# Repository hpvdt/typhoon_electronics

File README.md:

# Typhoon Electronics

The electronics system for Typhoon Streamliner

## Organization

There is a folder for each subsystem. Within each subsystem folder are `hardware` and `firmware` folders. Put hardware related files into the `hardware` folder, firmware in the `firmware` folder. Other folders can be added as needed: for example a `media` folder is handy for storing pictures related to a project which can be used in documentation.

## Conventions

Partly for consistency, partly for functionality; please follow the following conventions:

- Try to keep folder names to single words and all lowercase
- Use underscores to separate words in names (e.g. `board_rev1`). **DO NOT USE SPACES! ESPECIALLY FOR FOLDERS CONTAINING CODE!** Spaces in file paths may cause issues in compilers and such so best to avoid them entirely.

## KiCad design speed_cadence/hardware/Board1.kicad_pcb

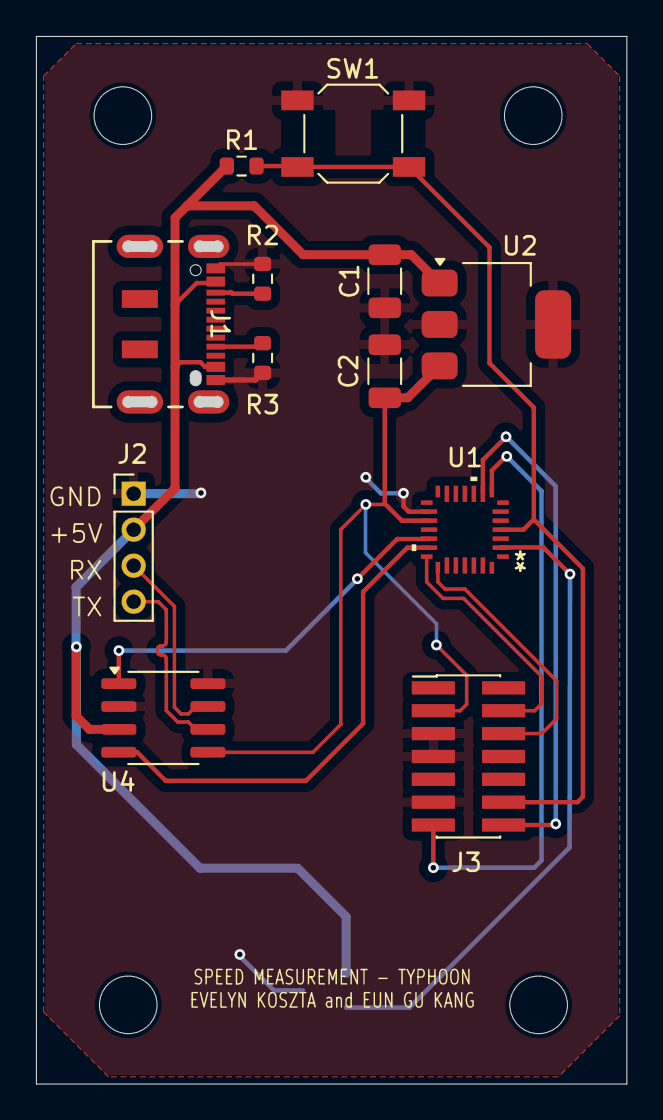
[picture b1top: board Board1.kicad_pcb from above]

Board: 2 copper layers, 32.8 x 58.2 mm, 17 parts (1 on the bottom side), 15 nets.

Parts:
C1: 0.47u; C_1206_3216Metric
C2: 22u; C_1206_3216Metric
H1, H2, H3, H4: MountingHole; MountingHole_3.2mm_M3_ISO14580
IC1: AH1912-W-7; SC-59
J1: DX07S016JA3R1500; CONN12_DX07S_JAE
J2: Conn_01x04_Pin; PinHeader_1x04_P2.00mm_Vertical
J3: Conn_ST_STDC14; PinHeader_2x07_P1.27mm_Vertical_SMD
R1: 10K; R_0603_1608Metric
R2, R3: 5.1k; R_0603_1608Metric
SW1: SW_Push; SW_SPST_SKQG_WithStem
U1: STM32F042G6U6TR; UFQFPN28-4x4mm-M
U2: TS2940CW33_RPG; SOT-223-3_TabPin2
U4: TJA1051T-3; SOIC-8_3.9x4.9mm_P1.27mm

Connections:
+3V3: C2.1, J3.3 (VCC), U1.17 (VDD), U2.3 (OUTPUT), U4.5 (VIO)
+5V: C1.1, IC1.1 (VDD), J1.2 (VBUS), J1.11 (VBUS), J2.2, R1.1, U2.1 (INPUT), U4.3 (VCC)
CAN+: J2.3, U4.7 (CANH)
CAN-: J2.4, U4.6 (CANL)
CAN_RX: U1.20 (PA10/PA12), U4.4 (RXD)
CAN_TX: U1.19 (PA9/PA11), U4.1 (TXD)
GND: C1.2, C2.2, IC1.3 (GND), J1.1 (GND), J1.12 (GND), J2.1, J3.5 (GND), J3.7 (GND), J3.11 (GNDDetect), R2.2, R3.2, SW1.2, U1.16 (VSS), U2.2 (GROUND_1), U4.2 (GND), U4.8 (S)
unnamed: IC1.2 (OUTPUT), U1.2 (PF0-OSC_IN)
unnamed: J1.3 (CC1), R2.1
unnamed: J1.9 (CC2), R3.1
Prog_RX: J3.13 (VCP_RX), U1.8 (PA2)
Prog_TX: J3.14 (VCP_TX), U1.9 (PA3)
RESET_PROG: J3.12 (~RST), R1.2, SW1.1, U1.4 (NRST)
codeclk: J3.6 (JCLK/SWCLK), U1.22 (PA14)
codeio: J3.4 (JTMS/SWDIO), U1.21 (PA13)

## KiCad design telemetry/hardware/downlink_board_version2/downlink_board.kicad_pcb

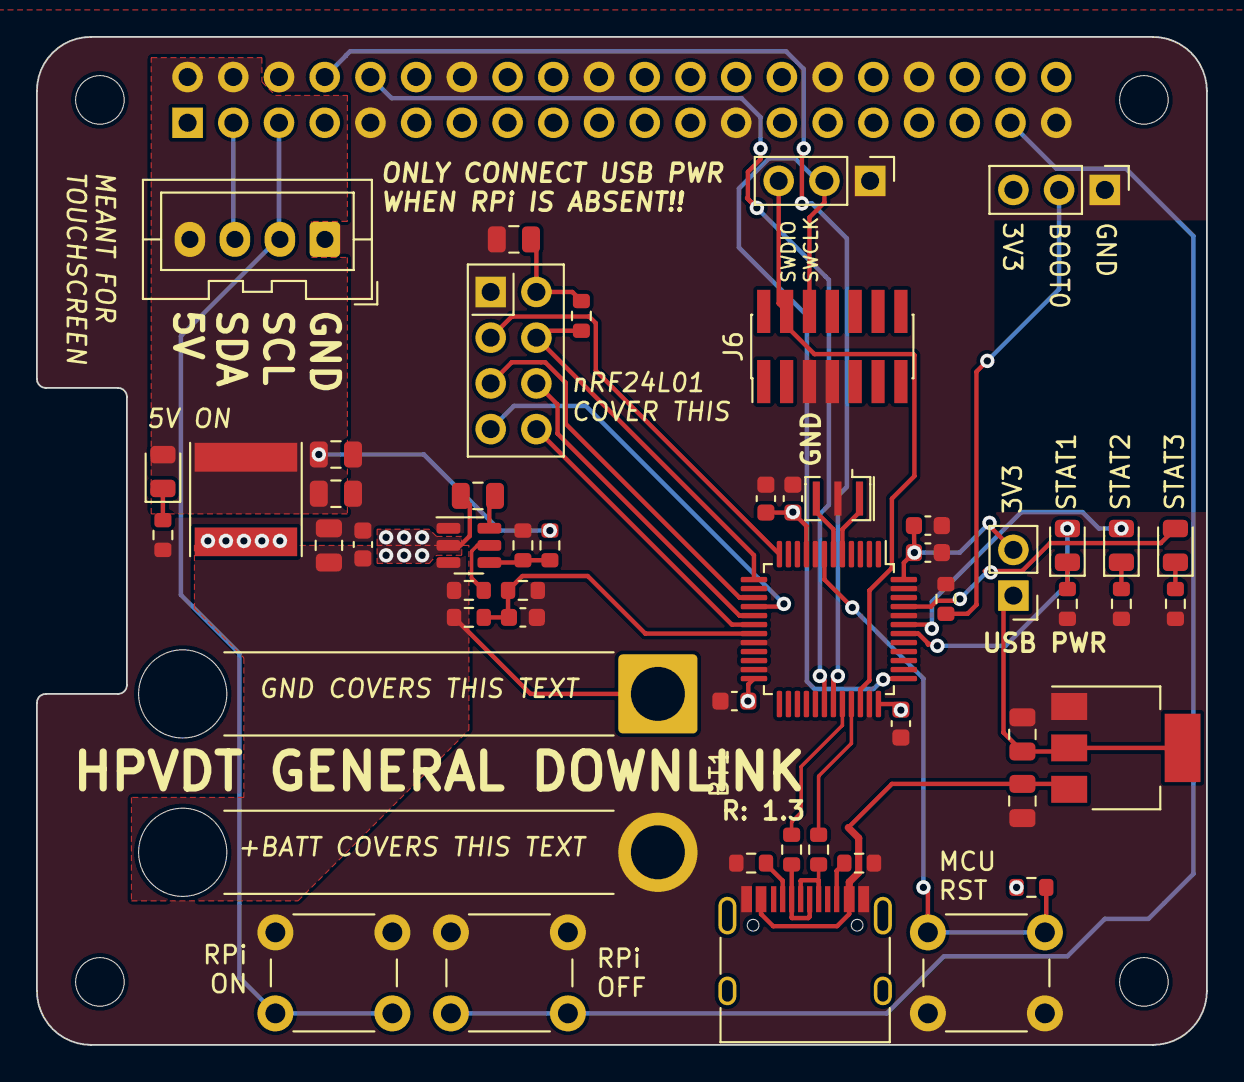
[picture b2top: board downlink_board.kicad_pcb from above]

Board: 2 copper layers, 65.0 x 56.0 mm, 56 parts (1 on the bottom side), 41 nets.

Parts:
BT1: Battery; SolderWire-2.5sqmm_1x02_P8.8mm_D2.4mm_OD4.4mm_Relief
C1, C2, C14: 10u; C_0805_2012Metric
C3, C8, C9, C10, C11, C13: 100n; C_0603_1608Metric
C4, C6, C7: 22u; C_0805_2012Metric
C5: 100n; C_0805_2012Metric
C12: 10n; C_0603_1608Metric
C15: 1u; C_0603_1608Metric
D1, D2, D3, D4: LED; LED_0805_2012Metric
J1: USB_C_Receptacle_USB2.0; USB_C_Receptacle_HRO_TYPE-C-31-M-12
J2: SCREEN; JST_XA_B04B-XASK-1_1x04_P2.50mm_Vertical
J3: GPIO; PinSocket_2x20_P2.54mm_Vertical
J4: PROGRAM; PinHeader_1x03_P2.54mm_Vertical
J6: Conn_ST_STDC14; PinHeader_2x07_P1.27mm_Vertical_SMD
JP1: USB_PWR; PinHeader_1x02_P2.54mm_Vertical
JP2: BOOT0; PinHeader_1x03_P2.54mm_Vertical
L1: 3u3; L_Taiyo-Yuden_NR-60xx
MH1, MH2, MH3, MH4: MountingHole_2.7mm_M2.5
R1, R2: 5.1k; R_0603_1608Metric
R3, R4: 22; R_0603_1608Metric
R5, R7, R9, R13, R14, R16: 10k; R_0603_1608Metric
R6, R15: 54k9; R_0603_1608Metric
R8, R10, R11, R12: 330; R_0603_1608Metric
SW1: RPi_{ON}; SW_PUSH_6mm_H4.3mm
SW2: RPi_{OFF}; SW_PUSH_6mm_H4.3mm
SW3: MCU_{RST}; SW_PUSH_6mm_H4.3mm
U1: AZ1117-3.3; SOT-223-3_TabPin2
U2: TPS563208DDCR; TSOT-23-6
U3: STM32F103C8Tx; LQFP-48_7x7mm_P0.5mm
U4: nRF24L01; nRF24L01_Breakout
Y1: 8M; Resonator_SMD_Murata_CSTxExxV-3Pin_3.0x1.1mm

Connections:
+3.3V: C8.2, C9.2, C10.2, C11.2, C12.2, C14.2, C15.2, J3.1, J3.17, JP1.2 (B), JP2.3 (B), R13.2, R14.2, U3.9 (VDDA), U3.24 (VDD), U3.36 (VDD), U3.48 (VDD), U4.2 (VCC)
+5V: C6.2, C7.2, D2.2 (A), J2.4, J3.2, J3.4, L1.2, R6.1
+BATT: BT1.1 (+), C1.2, C3.2, R5.1, R15.2, U2.3 (VIN)
/BATT_{DIV}: C13.2, R15.1, R16.2, U3.19 (PB1)
/BOOT0: JP2.2 (C), R9.2
/D+: J1.A6 (D+), J1.B6 (D+), R4.1
/D-: J1.A7 (D-), J1.B7 (D-), R3.1
/FB: R6.2, R7.2, U2.4 (VFB)
/GPIO26: J3.37, SW2.2
/MISO: U3.16 (PA6), U4.7 (MISO)
/MOSI: U3.17 (PA7), U4.6 (MOSI)
/RF_{EN}: U3.12 (PA2), U4.3 (CE)
/RF_{INT}: U3.18 (PB0), U4.8 (IRQ)
/RF_{SEL}: R14.1, U3.13 (PA3), U4.4 (~CSN)
/RPi_{RX}: J3.10, U3.30 (PA9)
/RPi_{TX}: J3.8, U3.31 (PA10)
/RST_{MCU}: R13.1, SW3.2, U3.7 (NRST)
/SCK: U3.15 (PA5), U4.5 (SCK)
/SCL: J2.2, J3.5, SW1.2
/SDA: J2.3, J3.3
/SDWIO: J4.3, J6.4 (JTMS/SWDIO), U3.34 (PA13)
/STATUS_{1}: D1.2 (A), U3.42 (PB6)
/STATUS_{2}: D3.2 (A), U3.43 (PB7)
/STATUS_{3}: D4.2 (A), U3.45 (PB8)
/SWCLK: J4.2, J6.6 (JCLK/SWCLK), U3.37 (PA14)
/USB_D+: R4.2, U3.33 (PA12)
/USB_D-: R3.2, U3.32 (PA11)
GND: BT1.2 (-), C1.1, C2.1, C3.1, C4.1, C6.1, C7.1, C8.1, C9.1, C10.1, C11.1, C12.1, C13.1, C14.1, C15.1, J1.A1 (GND), J1.A12 (GND), J1.B1 (GND), J1.B12 (GND), J2.1, J3.6, J3.9, J3.14, J3.20, J3.25, J3.30, J3.34, J3.39, J4.1, J6.5 (GND), J6.7 (GND), JP2.1 (A), R1.2, R2.2, R7.1, R8.1, R9.1, R10.1, R11.1, R12.1, R16.1, SW1.1, SW2.1, SW3.1, U1.1 (GND), U2.1 (GND), U3.8 (VSSA), U3.20 (PB2), U3.23 (VSS), U3.35 (VSS), U3.44 (BOOT0), U3.47 (VSS), U4.1 (GND), Y1.2
unnamed: D1.1 (K), R8.2
unnamed: D2.1 (K), R10.2
unnamed: D3.1 (K), R11.2
unnamed: D4.1 (K), R12.2
unnamed: J1.A5 (CC1), R1.1
unnamed: J1.B5 (CC2), R2.1
unnamed: C4.2, JP1.1 (A), U1.2 (VO)
unnamed: C2.2, J1.A4 (VBUS), J1.A9 (VBUS), J1.B4 (VBUS), J1.B9 (VBUS), U1.3 (VI)
unnamed: R5.2, U2.5 (EN)
unnamed: C5.2, L1.1, U2.2 (SW)
unnamed: C5.1, U2.6 (VBST)
unnamed: U3.5 (PD0), Y1.1
unnamed: U3.6 (PD1), Y1.3

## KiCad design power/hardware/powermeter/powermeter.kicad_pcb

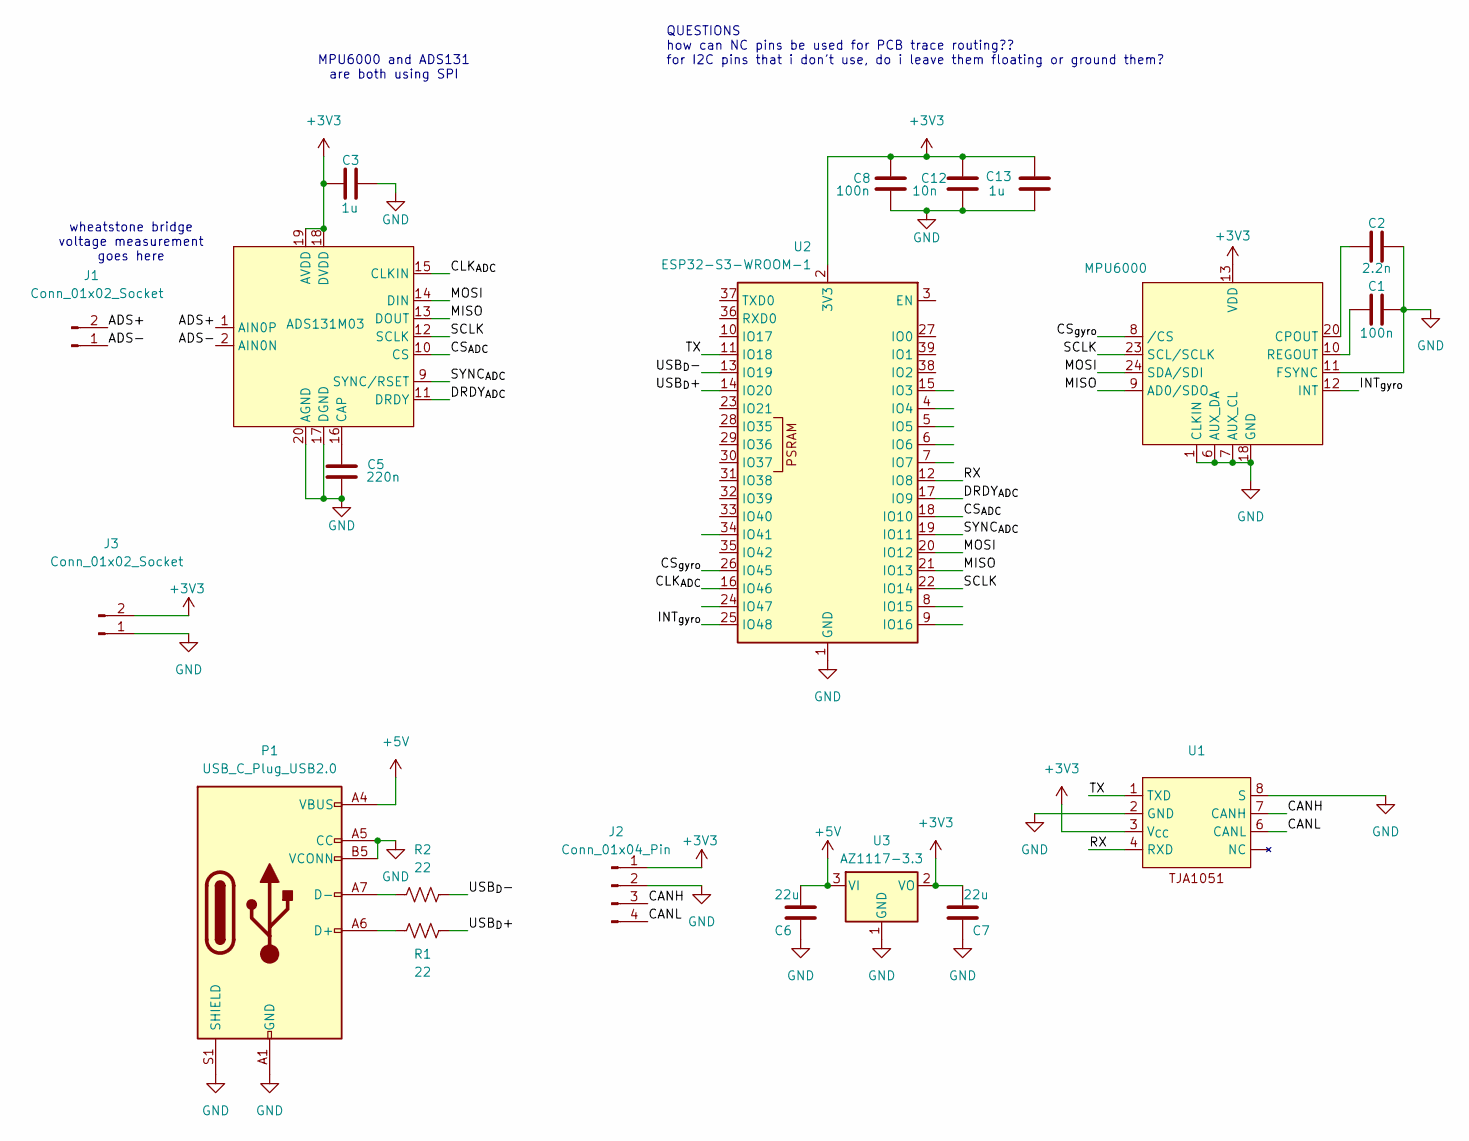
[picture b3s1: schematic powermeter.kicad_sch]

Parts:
ADS131M03: ads
C1, C8: 100n; C_0603_1608Metric
C2: 2.2n; C_0603_1608Metric
C3, C13: 1u; C_0603_1608Metric
C5: 220n; C_0603_1608Metric
C6, C7: 22u; C_0603_1608Metric
C12: 10n; C_0603_1608Metric
J1: Conn_01x02_Socket; PinHeader_1x02_P2.00mm_Vertical
J2: Conn_01x04_Pin; PinHeader_1x04_P2.00mm_Vertical
J3: Conn_01x02_Socket; AMASS_XT30U-M_1x02_P5.0mm_Vertical
MPU6000: QFN24_4X4X0P9_IVS
P1: USB_C_Plug_USB2.0; USB_C_Receptacle_HRO_TYPE-C-31-M-12
R1, R2: 22; R_0603_1608Metric
U1: SO-8_3.9x4.9mm_P1.27mm
U2: ESP32-S3-WROOM-1
U3: AZ1117-3.3; SOT-223-3_TabPin2

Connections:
+3V3: ADS131M03.18 (DVDD), ADS131M03.19 (AVDD), C3.2, C7.2, C8.2, C12.2, C13.2, J2.1, J3.2, MPU6000.13 (VDD), U1.3 (V_{CC}), U2.2 (3V3), U3.2 (VO)
+5V: C6.2, P1.A4 (VBUS), P1.A9 (VBUS), P1.B4 (VBUS), P1.B9 (VBUS), U3.3 (VI)
/ADS+: ADS131M03.1 (AIN0P), J1.2
/ADS-: ADS131M03.2 (AIN0N), J1.1
/CANH: J2.3, U1.7 (CANH)
/CANL: J2.4, U1.6 (CANL)
/CLK_{ADC}: ADS131M03.15 (CLKIN), U2.16 (IO46)
/CS_{ADC}: ADS131M03.10 (CS), U2.18 (IO10)
/CS_{gyro}: MPU6000.8 (/CS), U2.26 (IO45)
/DRDY_{ADC}: ADS131M03.11 (DRDY), U2.17 (IO9)
/INT_{gyro}: MPU6000.12 (INT), U2.25 (IO48)
/MISO: ADS131M03.13 (DOUT), MPU6000.9 (AD0/SDO), U2.21 (IO13)
/MOSI: ADS131M03.14 (DIN), MPU6000.24 (SDA/SDI), U2.20 (IO12)
/RX: U1.4 (RXD), U2.12 (IO8)
/SCLK: ADS131M03.12 (SCLK), MPU6000.23 (SCL/SCLK), U2.22 (IO14)
/SYNC_{ADC}: ADS131M03.9 (SYNC/RSET), U2.19 (IO11)
/TX: U1.1 (TXD), U2.11 (IO18)
/USB_{D}+: R1.2, U2.14 (IO20)
/USB_{D}-: R2.2, U2.13 (IO19)
GND: ADS131M03.17 (DGND), ADS131M03.20 (AGND), C1.1, C2.1, C3.1, C5.1, C6.1, C7.1, C8.1, C12.1, C13.1, J2.2, J3.1, MPU6000.1 (CLKIN), MPU6000.6 (AUX_DA), MPU6000.7 (AUX_CL), MPU6000.11 (FSYNC), MPU6000.18 (GND), P1.A1 (GND), P1.A5 (CC), P1.A12 (GND), P1.B1 (GND), P1.B5 (VCONN), P1.B12 (GND), P1.S1 (SHIELD), U1.2 (GND), U1.8 (S), U2.1 (GND), U2.40 (GND), U2.41 (GND), U3.1 (GND)
unnamed: ADS131M03.16 (CAP), C5.2
unnamed: C2.2, MPU6000.20 (CPOUT)
unnamed: C1.2, MPU6000.10 (REGOUT)
unnamed: P1.A6 (D+), R1.1
unnamed: P1.A7 (D-), R2.1

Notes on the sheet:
wheatstone bridge voltage measurement goes here
MPU6000 and ADS131 are both using SPI
QUESTIONS how can NC pins be used for PCB trace routing?? for I2C pins that i don't use, do i leave them floating or ground them?

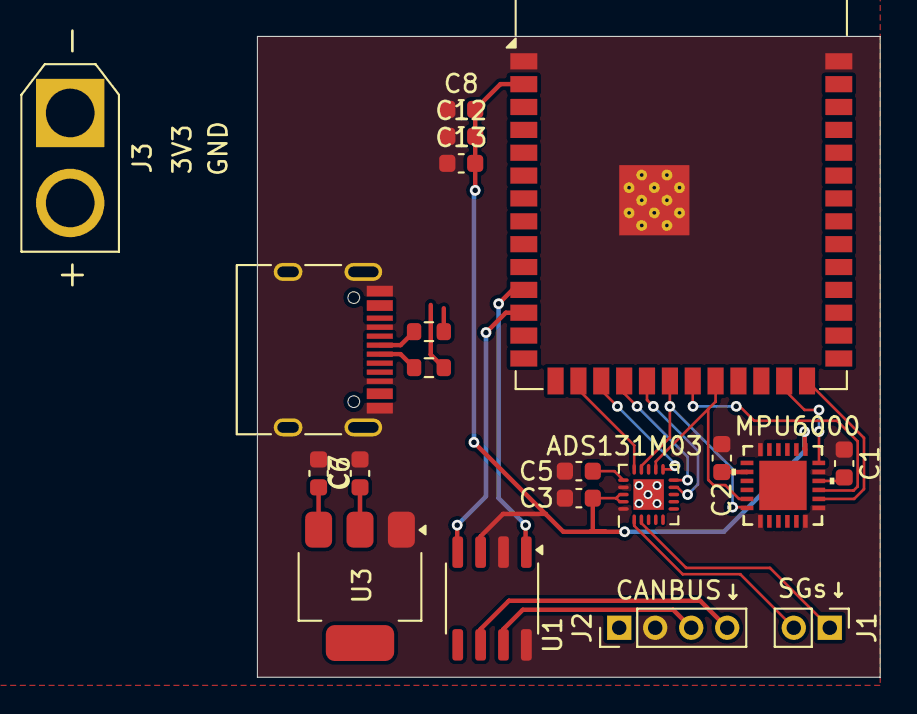
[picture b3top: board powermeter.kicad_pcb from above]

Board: 2 copper layers, 34.6 x 35.6 mm, 20 parts (0 on the bottom side), 25 nets.

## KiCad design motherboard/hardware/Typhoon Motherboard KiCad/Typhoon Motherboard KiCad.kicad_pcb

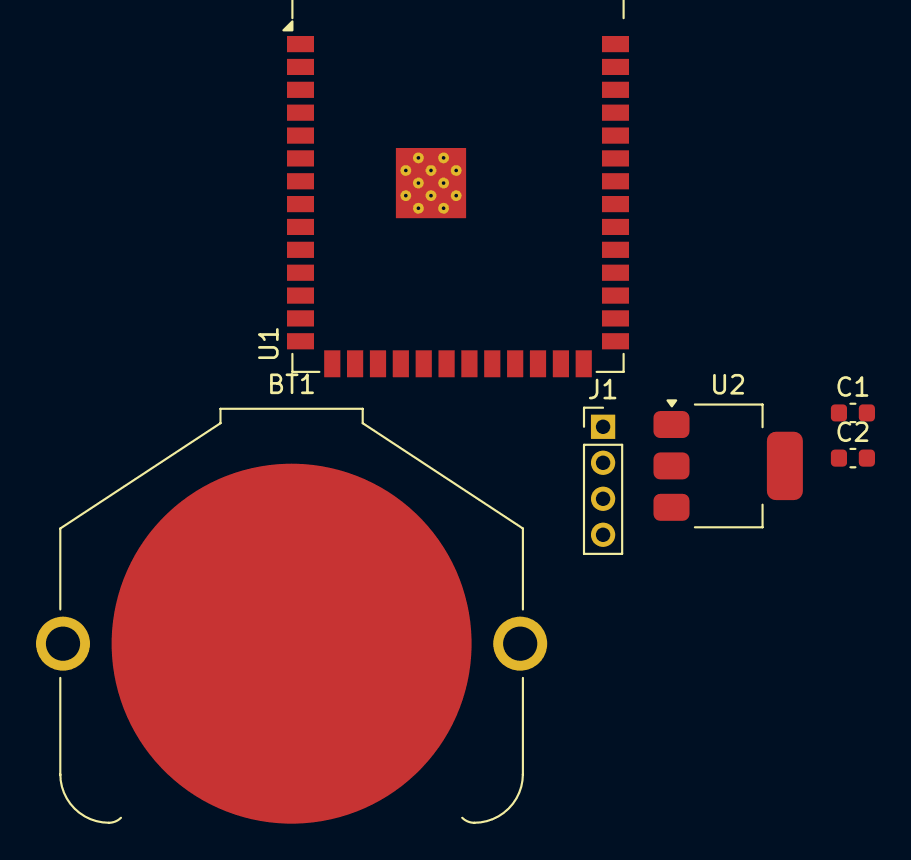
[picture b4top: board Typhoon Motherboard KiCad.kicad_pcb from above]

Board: 2 copper layers, 6 parts (0 on the bottom side), 4 nets, no tracks yet.

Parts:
BT1: Battery_Cell; BatteryHolder_Keystone_3009_1x2450
C1, C2: 22u; C_0603_1608Metric
J1: Conn_01x04_Pin; PinHeader_1x04_P2.00mm_Vertical
U1: ESP32-S3-WROOM-1
U2: AZ1117-3.3; SOT-223-3_TabPin2

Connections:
+3.3V: C2.2, U2.2 (VO)
+3V3: BT1.1 (+), J1.1, U1.2 (3V3)
+5V: C1.2, U2.3 (VI)
GND: BT1.2 (-), C1.1, C2.1, J1.2, U1.1 (GND), U1.40 (GND), U1.41 (GND), U2.1 (GND)

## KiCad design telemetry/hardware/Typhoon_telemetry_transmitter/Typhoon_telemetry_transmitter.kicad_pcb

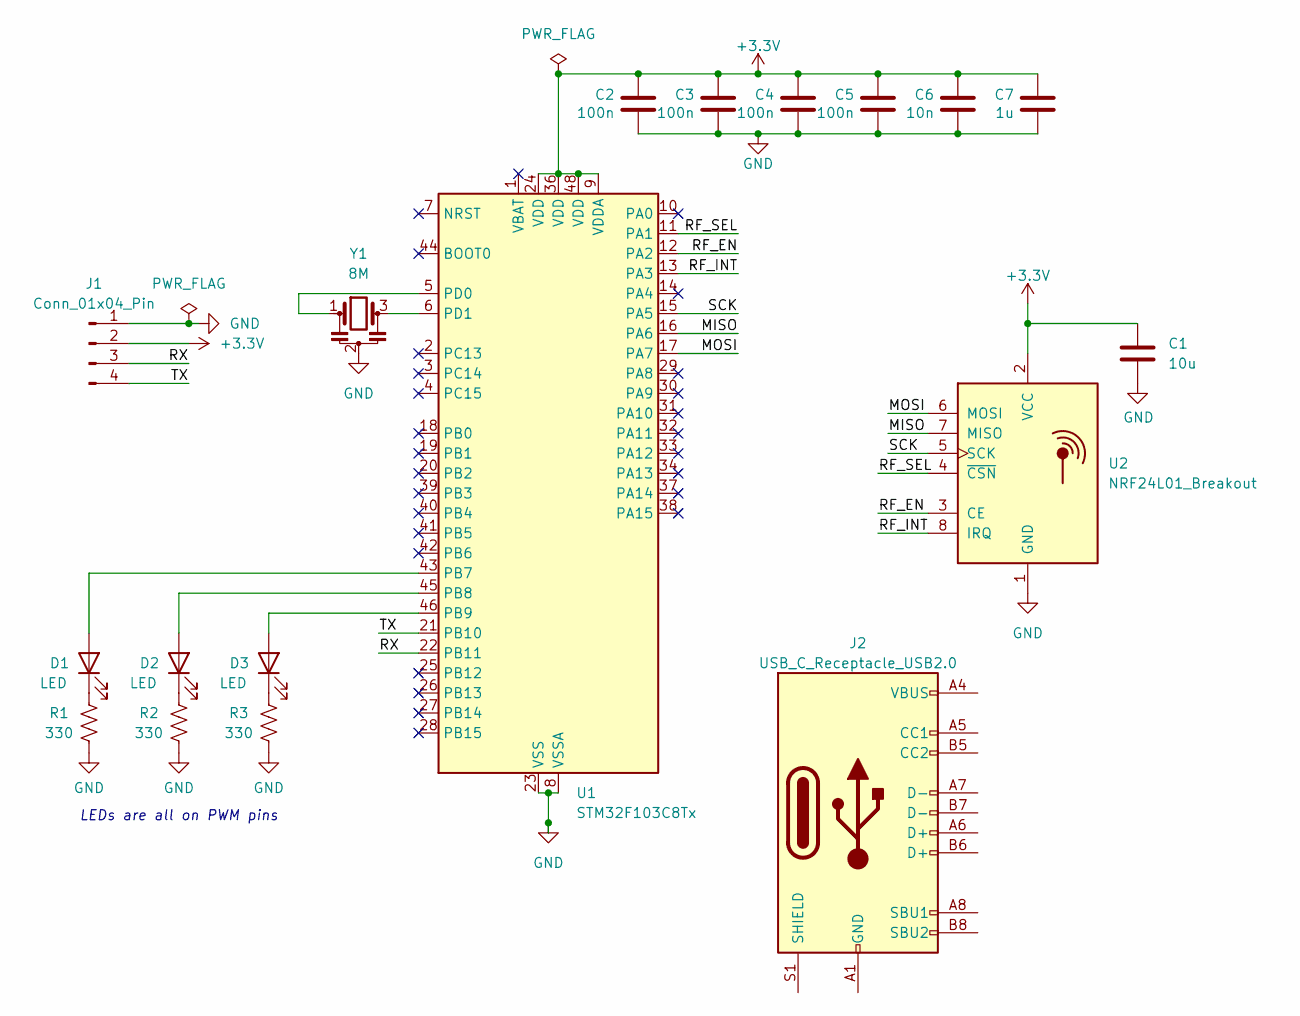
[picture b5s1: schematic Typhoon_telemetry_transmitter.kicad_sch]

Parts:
C1: 10u; C_0805_2012Metric
C2, C3, C4, C5: 100n; C_0603_1608Metric
C6: 10n; C_0603_1608Metric
C7: 1u; C_0603_1608Metric
D1, D2, D3: LED; LED_0805_2012Metric
J1: Conn_01x04_Pin; PinHeader_1x04_P1.00mm_Vertical
J2: USB_C_Receptacle_USB2.0; USB_C_Receptacle_HRO_TYPE-C-31-M-12
R1, R2, R3: 330; R_0603_1608Metric
U1: STM32F103C8Tx; LQFP-48_7x7mm_P0.5mm
U2: NRF24L01_Breakout; nRF24L01_Breakout
Y1: 8M; Resonator_SMD_Murata_CSTxExxV-3Pin_3.0x1.1mm

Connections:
+3.3V: C1.2, C2.2, C3.2, C4.2, C5.2, C6.2, C7.2, J1.2, U1.9 (VDDA), U1.24 (VDD), U1.36 (VDD), U1.48 (VDD), U2.2 (VCC); also elsewhere on the board
/MISO: U1.16 (PA6), U2.7 (MISO)
/MOSI: U1.17 (PA7), U2.6 (MOSI)
/Programming_RX: U1.31 (PA10); also elsewhere on the board
/Programming_TX: U1.30 (PA9); also elsewhere on the board
/RF_EN: U1.12 (PA2), U2.3 (CE)
/RF_INT: U1.13 (PA3), U2.8 (IRQ)
/RF_SEL: U1.11 (PA1), U2.4 (~CSN)
/RX: J1.3, U1.22 (PB11)
/Reset: U1.7 (NRST); also elsewhere on the board
/SCK: U1.15 (PA5), U2.5 (SCK)
/TX: J1.4, U1.21 (PB10)
/codeclk: U1.37 (PA14); also elsewhere on the board
/codeio: U1.34 (PA13); also elsewhere on the board
GND: C1.1, C2.1, C3.1, C4.1, C5.1, C6.1, C7.1, J1.1, R1.1, R2.1, R3.1, U1.8 (VSSA), U1.23 (VSS), U1.35 (VSS), U1.47 (VSS), U2.1 (GND), Y1.2; also elsewhere on the board
unnamed: D1.2 (A), U1.43 (PB7)
unnamed: D1.1 (K), R1.2
unnamed: D2.2 (A), U1.45 (PB8)
unnamed: D2.1 (K), R2.2
unnamed: D3.2 (A), U1.46 (PB9)
unnamed: D3.1 (K), R3.2
unnamed: J2.A1 (GND), J2.A12 (GND), J2.B1 (GND), J2.B12 (GND)
unnamed: J2.A4 (VBUS), J2.A9 (VBUS), J2.B4 (VBUS), J2.B9 (VBUS)
unnamed: U1.5 (PD0), Y1.1
unnamed: U1.6 (PD1), Y1.3

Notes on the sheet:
LEDs are all on PWM pins

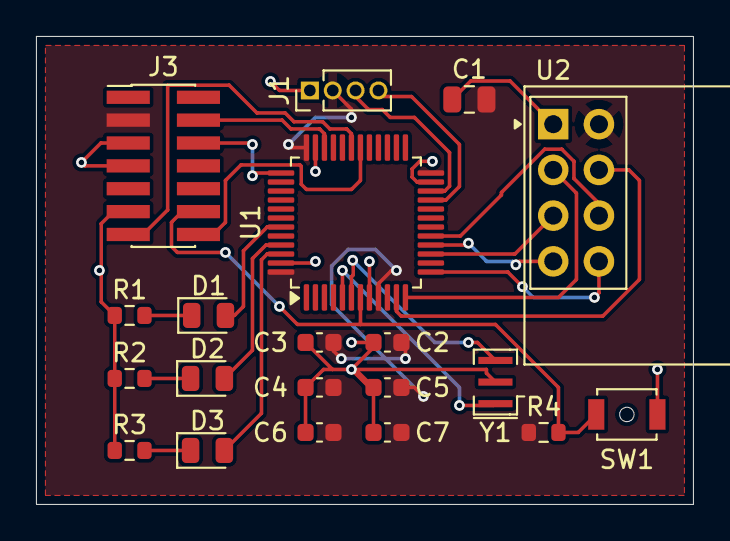
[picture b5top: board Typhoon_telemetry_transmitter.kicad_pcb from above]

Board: 2 copper layers, 36.5 x 26.0 mm, 20 parts (0 on the bottom side), 23 nets.

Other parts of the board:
J3: Conn_ST_STDC14; PinHeader_2x07_P1.27mm_Vertical_SMD
R4: 10k; R_0603_1608Metric
SW1: SW_Push; SW_SPST_B3U-1000P-B

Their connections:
+3.3V: J3.3 (VCC), R4.1; also elsewhere on the board
/Programming_RX: J3.13 (VCP_RX); also elsewhere on the board
/Programming_TX: J3.14 (VCP_TX); also elsewhere on the board
/Reset: J3.12 (~RST), R4.2, SW1.2; also elsewhere on the board
/codeclk: J3.6 (JCLK/SWCLK); also elsewhere on the board
/codeio: J3.4 (JTMS/SWDIO); also elsewhere on the board
GND: J3.5 (GND), J3.7 (GND), J3.11 (GNDDetect), SW1.1; also elsewhere on the board

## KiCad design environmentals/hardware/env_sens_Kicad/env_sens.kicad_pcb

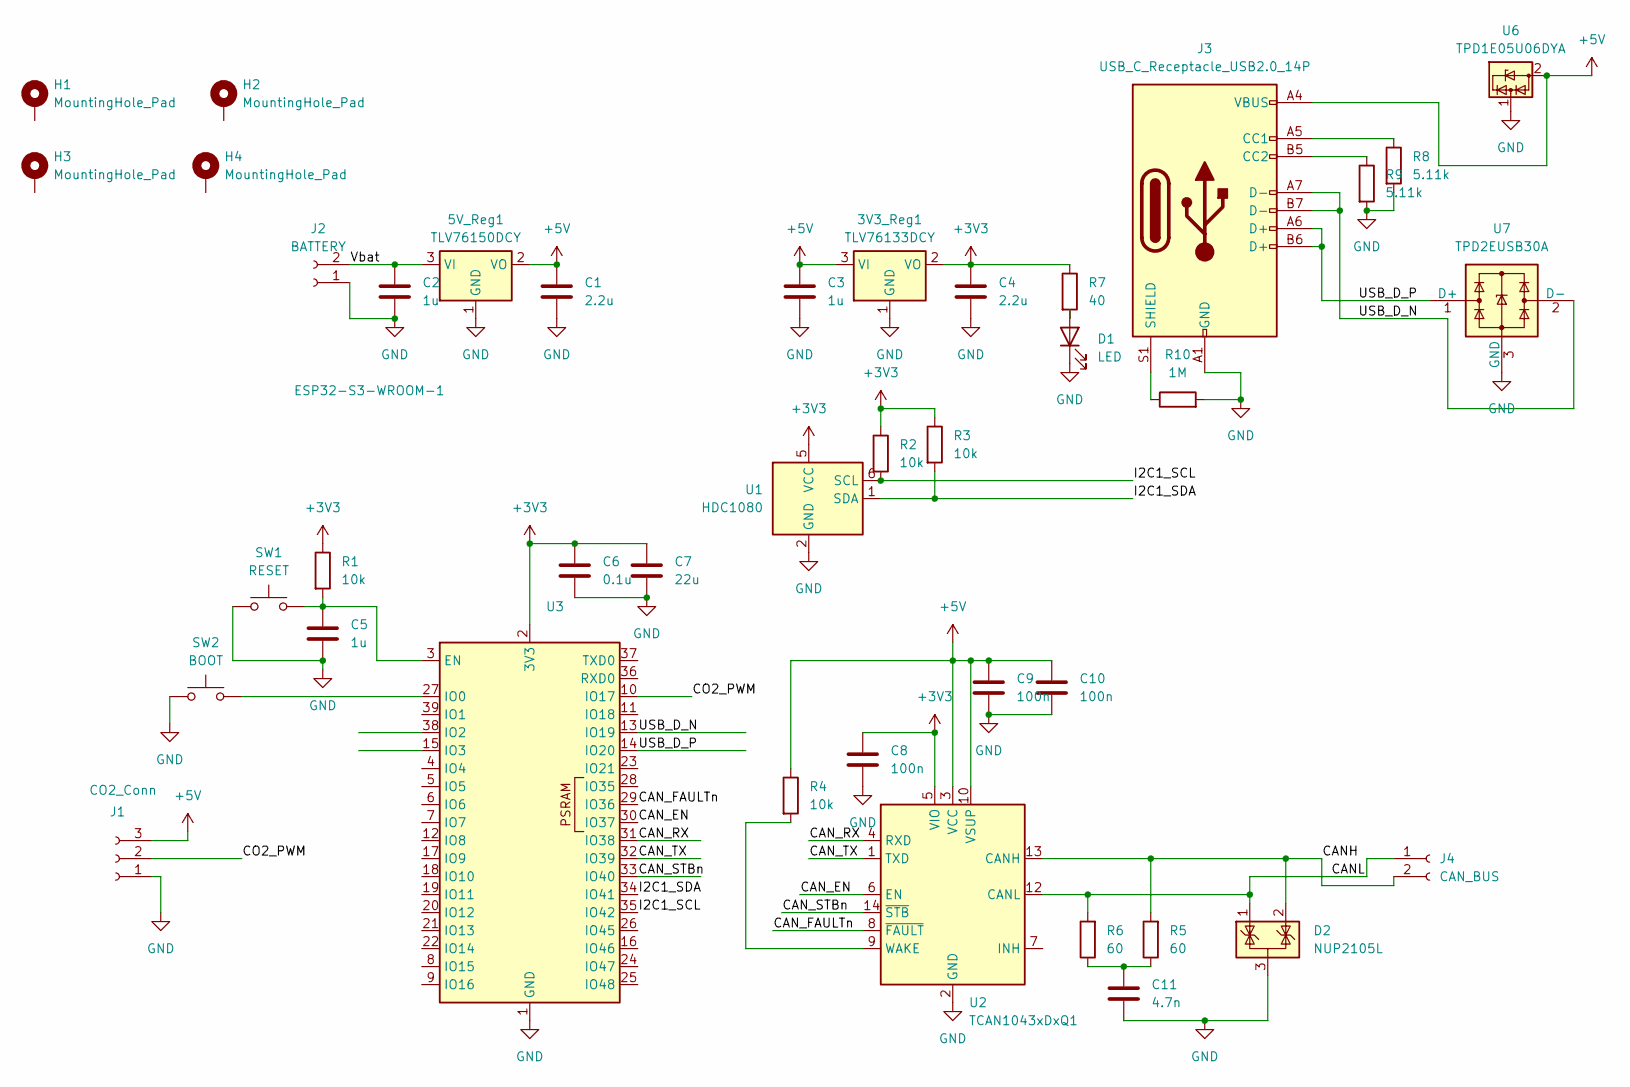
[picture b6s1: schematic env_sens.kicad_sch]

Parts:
3V3_Reg1: TLV76133DCY; SOT-223-3_TabPin2
5V_Reg1: TLV76150DCY; SOT-223-3_TabPin2
C1, C4: 2.2u; C_0805_2012Metric_Pad1.18x1.45mm_HandSolder
C2, C3, C5: 1u; C_0805_2012Metric_Pad1.18x1.45mm_HandSolder
C6: 0.1u; C_0805_2012Metric_Pad1.18x1.45mm_HandSolder
C7: 22u; C_0805_2012Metric_Pad1.18x1.45mm_HandSolder
C8, C9, C10: 100n; C_0805_2012Metric_Pad1.18x1.45mm_HandSolder
C11: 4.7n; C_0603_1608Metric_Pad1.08x0.95mm_HandSolder
D1: LED; LED_0805_2012Metric_Pad1.15x1.40mm_HandSolder
D2: NUP2105L; SOT-23
H1, H2, H3, H4: MountingHole_Pad; MountingHole_3.2mm_M3_DIN965_Pad_TopBottom
J1: CO2_Conn; JST_XH_S3B-XH-A_1x03_P2.50mm_Horizontal
J2: BATTERY; AMASS_XT60PW-M_1x02_P7.20mm_Horizontal
J3: USB_C_Receptacle_USB2.0_14P; USB_C_Receptacle_Amphenol_12401610E4-2A
J4: CAN_BUS; JST_PH_S2B-PH-SM4-TB_1x02-1MP_P2.00mm_Horizontal
R1, R2, R3, R4: 10k; R_0805_2012Metric_Pad1.20x1.40mm_HandSolder
R5, R6: 60; R_0603_1608Metric_Pad0.98x0.95mm_HandSolder
R7: 40; R_0805_2012Metric_Pad1.20x1.40mm_HandSolder
R8, R9: 5.11k; R_0805_2012Metric_Pad1.20x1.40mm_HandSolder
R10: 1M; R_0805_2012Metric_Pad1.20x1.40mm_HandSolder
SW1: RESET; SW_PUSH_6mm
SW2: BOOT; SW_PUSH_6mm
U1: HDC1080; Texas_PWSON-N6
U2: TCAN1043xDxQ1; SOIC-14_3.9x8.7mm_P1.27mm
U3: ESP32-S3-WROOM-1
U6: TPD1E05U06DYA; D_SOD-523
U7: TPD2EUSB30A; Texas_DRT-3

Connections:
+3V3: 3V3_Reg1.2 (VO), C4.1, C6.1, C7.1, C8.1, R1.1, R2.1, R3.1, R7.1, U1.5 (VCC), U2.5 (VIO), U3.2 (3V3)
+5V: 3V3_Reg1.3 (VI), 5V_Reg1.2 (VO), C1.1, C3.1, C9.1, C10.1, J1.3, J3.A4 (VBUS), J3.A9 (VBUS), J3.B4 (VBUS), J3.B9 (VBUS), R4.1, U2.3 (VCC), U2.10 (VSUP), U6.2 (GND)
/CANH: D2.2 (K), J4.2, R5.2, U2.13 (CANH)
/CANL: D2.1 (K), J4.1, R6.2, U2.12 (CANL)
/CAN_EN: U2.6 (EN), U3.30 (IO37)
/CAN_FAULTn: U2.8 (~FAULT), U3.29 (IO36)
/CAN_RX: U2.4 (RXD), U3.31 (IO38)
/CAN_STBn: U2.14 (~STB), U3.33 (IO40)
/CAN_TX: U2.1 (TXD), U3.32 (IO39)
/CO2_PWM: J1.2, U3.10 (IO17)
/I2C1_SCL: R2.2, U1.6 (SCL), U3.35 (IO42)
/I2C1_SDA: R3.2, U1.1 (SDA), U3.34 (IO41)
/USB_D_N: J3.A7 (D-), J3.B7 (D-), U3.13 (IO19), U7.2 (D-)
/USB_D_P: J3.A6 (D+), J3.B6 (D+), U3.14 (IO20), U7.1 (D+)
/Vbat: 5V_Reg1.3 (VI), C2.1, J2.2
GND: 3V3_Reg1.1 (GND), 5V_Reg1.1 (GND), C1.2, C2.2, C3.2, C4.2, C5.2, C6.2, C7.2, C8.2, C9.2, C10.2, C11.2, D1.1 (K), D2.3 (A), J1.1, J2.1, J3.A1 (GND), J3.A12 (GND), J3.B1 (GND), J3.B12 (GND), R8.2, R9.2, R10.2, SW1.1, SW2.1, U1.2 (GND), U2.2 (GND), U3.1 (GND), U3.40 (GND), U3.41 (GND), U6.1 (I/O), U7.3 (GND)
unnamed: C11.1, R5.1, R6.1
unnamed: D1.2 (A), R7.2
unnamed: J3.A5 (CC1), R8.1
unnamed: J3.B5 (CC2), R9.1
unnamed: J3.S1 (SHIELD), R10.1
unnamed: R4.2, U2.9 (WAKE)
unnamed: C5.1, R1.2, SW1.2, U3.3 (EN)
unnamed: SW2.2, U3.27 (IO0)

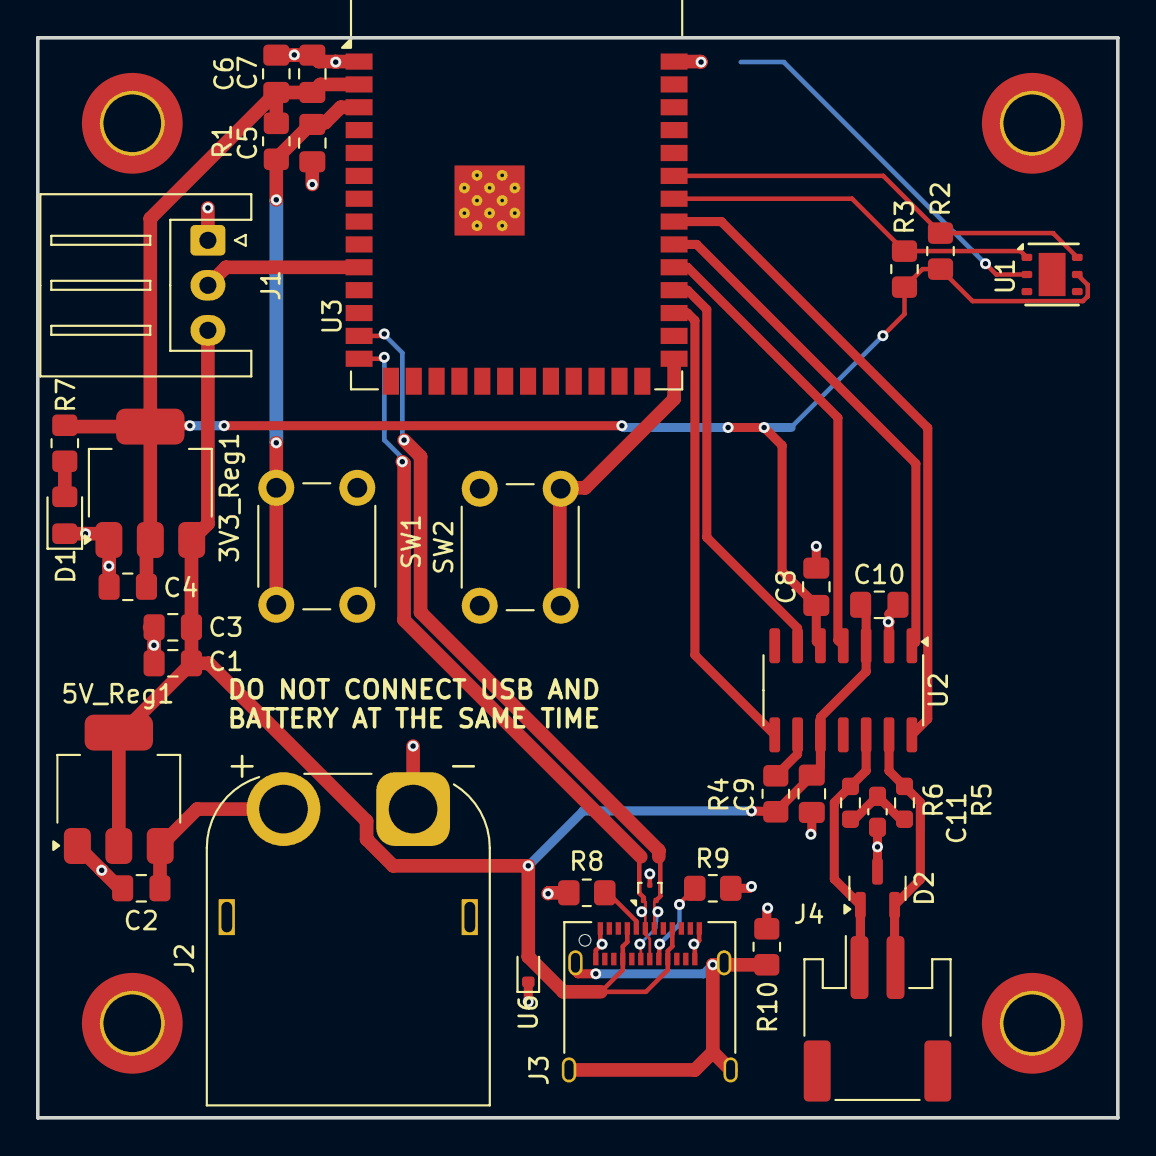
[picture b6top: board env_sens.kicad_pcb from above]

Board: 2 copper layers, 60.0 x 60.0 mm, 40 parts (0 on the bottom side), 24 nets.

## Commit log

2024-05-18 Update README.md
    updated readme
2024-05-18 Added Motherboard KiCad Files
2024-05-18 Minor changes
2024-05-22 Create README copy.md
    test commit
2024-05-22 added files
    added files
2024-05-24 code for reading power from powertap pedals over ble On branch main Your branch is up to date with 'origin/main'.
2024-05-24 test :)
2024-05-25 Major components added
2024-05-27 Connected voltage regulator and fixed labels
    Changed the VDD labels to the global labels that show voltage values. Added the capacitors for the voltage regulator
2024-05-27 Added footprints for capacitors
2024-05-30 Updated voltage regulator output
2024-05-30 Connected USB-C to microcontroller
2024-05-30 Resistors named
2024-05-31 Fixed "unable to find symbol" issues
2024-05-31 Fixed power outputs
2024-05-31 Changed ground pin to passive
2024-05-31 added cadence but limited to ~60rpm right now
2024-05-31 removed test file
2024-06-01 Excluded error
    Reverted the symbol pin change (GND to passive instead of power output) to just ignore the error as per Savo's advice.
2024-06-01 Preliminary PCB placement
2024-06-05 added most recent motherboard files
2024-06-05 fixed problem where cadence was maxxed out at 60rpm
2024-06-05 Environmental board schematic
2024-06-05 Removed UART
2024-06-05 fixed bad cadence values when connection starts up
2024-06-05 added v reg
2024-06-05 Added final pins and finished physical layout
2024-06-06 added header
2024-06-07 Finished environmental board layout
2024-06-08 Added the tracks and tried fixing the outline but didn’t work for some reason, even if it is a polygon. I think it doesn’t like that its angled...
2024-06-08 Fixed 3.3v and 5v connections to J1
2024-06-11 Added mounting holes
2024-06-13 Re-added the GND fill
2024-06-13 Replaced things
2024-06-14 New routing
2024-06-14 added ground pour
2024-06-14 updated tracks
2024-06-14 edited the board outline
2024-06-14 labelled header pins
2024-06-14 Changes of font
2024-06-14 added new symbol for TJA1051
2024-06-21 Added programmer/debugger connector
2024-06-21 Added connector for debugger to PCB
2024-06-21 PCB rework
2024-06-21 added footprint for CAN transceiver
2024-06-21 updated schematic
2024-06-28 added pcb
2024-06-28 Added XT60 connector
    Where does it connect to tho, still need to add that
2024-06-28 updated pcb
2024-07-01 Added in connector for "battery" to PCB layout
    There are 37 errors to either ignore or fix, but they should all be reviewed.
2024-07-01 Fixed alignment of silkscreen.
2024-07-03 Orientation
2024-07-03 flipped connector
2024-07-06 Removed battery connector
2024-07-06 Create downlink_board_version2
2024-07-06 Create downlink_board_v2
2024-07-06 Create downlink_v2
2024-07-06 Initial commit of downlink board v2
2024-07-06 Fixed "schematic STM32_ library not fount" error
2024-07-08 Added the CAN transciever
2024-08-30 Updated board
2024-08-30 Updated PCB with refined connections and transciever
2024-09-17 Updated differential pair routing
    CANH is now CAN+
    CANL is now CAN- for KiCAD to recognize the differential pair.
2024-10-18 Updated fill for differential pair
